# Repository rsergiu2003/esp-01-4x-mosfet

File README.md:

# esp-01-4x-mosfet
esp-01 extension board, with 4 mosfet transistors independently controlled, also has 1 power led and 4 status leds, and 3.3v stabilizations (can be powered up to 30V)

## Features
  - 4 mosfet transistors, connected to an pinheads
  - supports up to 30V DC (depending on the used mosfets)
  - no separate power needed for the ESP-01
  - 3.3 Voltage stabilizer
  - capacitor for voltage fluctuations
  - power indicator LED
  - status LED for each mosfet (so you can se if it's enabled or no)
  
## Testing
The board was tested with 12V comuper fans

## Software
Here are some repositories you can check out for using with this board.

## 3D Model

## More info
If you want more info feel free to leave me a message !

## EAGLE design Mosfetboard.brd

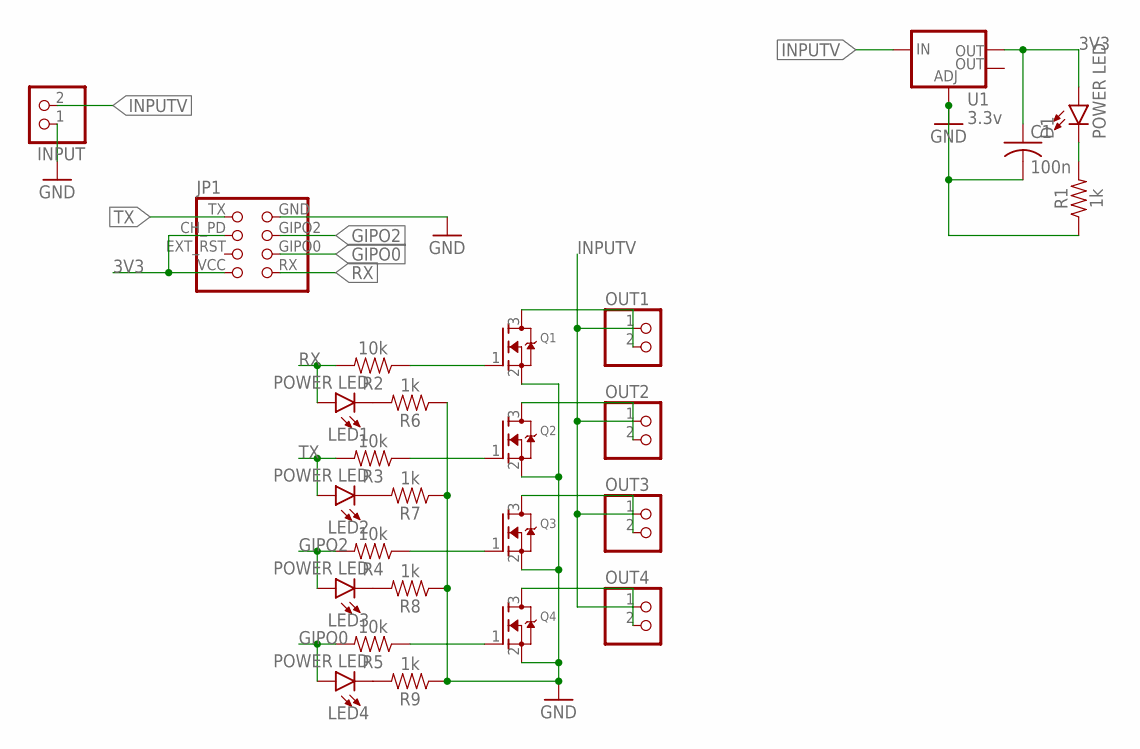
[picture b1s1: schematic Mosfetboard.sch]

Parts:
C1: 100n; C1206K
D1: POWER LED; LED-0805
INPUT: PINHD-1X2; 1X02
JP1: ESP-01-FEMALE
LED1, LED2, LED3, LED4: POWER LED; LED-0805
OUT1, OUT2, OUT3, OUT4: PINHD-1X2; 1X02
Q1, Q2, Q3, Q4: MOSFET-NREFLOW; SOT23
R1, R6, R7, R8, R9: 1k; 0805
R2, R3, R4, R5: 10k; 0805
U1: 3.3v; SOT223

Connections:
3V3: C1.1, D1.+ (A), JP1.CH_PD (CHIP_EN), JP1.VCC, U1.2 (OUT)
GIPO0: JP1.GIPO0, LED4.+ (A), R5.2
GIPO2: JP1.GIPO2, LED3.+ (A), R4.2
GND: C1.2, INPUT.1, JP1.GND, Q1.2 (S), Q2.2 (S), Q3.2 (S), Q4.2 (S), R1.1, R6.1, R7.1, R8.1, R9.1, U1.1 (ADJ)
INPUTV: INPUT.2, OUT1.1, OUT2.1, OUT3.1, OUT4.1, U1.3 (IN)
unnamed: OUT1.2, Q1.3 (D)
unnamed: OUT2.2, Q2.3 (D)
unnamed: OUT3.2, Q3.3 (D)
unnamed: OUT4.2, Q4.3 (D)
unnamed: D1.- (C), R1.2
unnamed: Q1.1 (G), R2.1
unnamed: Q2.1 (G), R3.1
unnamed: Q3.1 (G), R4.1
unnamed: Q4.1 (G), R5.1
unnamed: LED1.- (C), R6.2
unnamed: LED2.- (C), R7.2
unnamed: LED3.- (C), R8.2
unnamed: LED4.- (C), R9.2
RX: JP1.RX, LED1.+ (A), R2.2
TX: JP1.TX, LED2.+ (A), R3.2

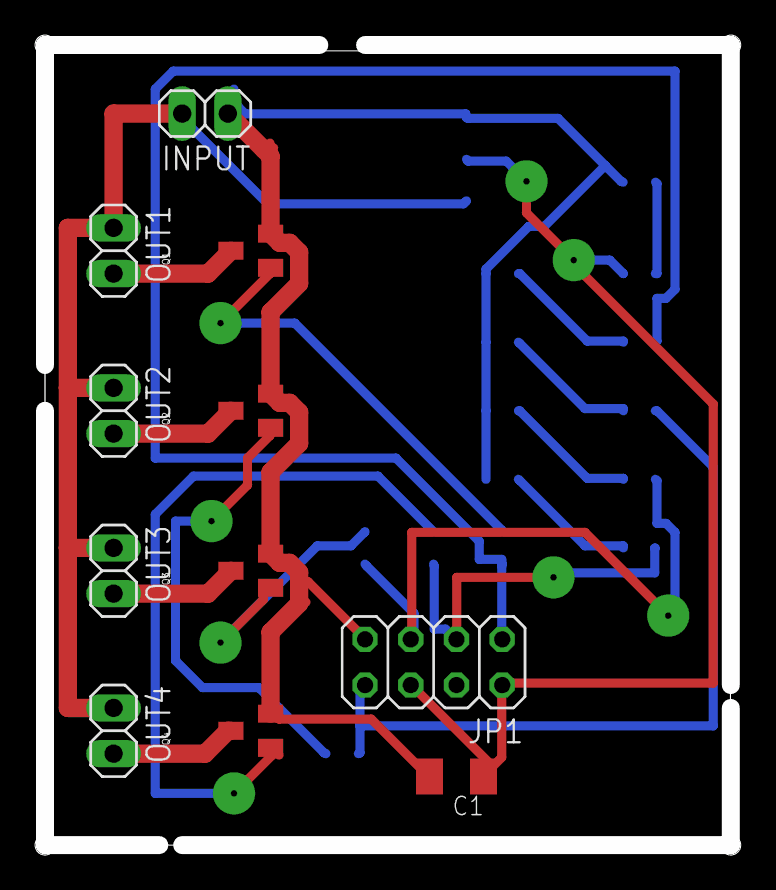
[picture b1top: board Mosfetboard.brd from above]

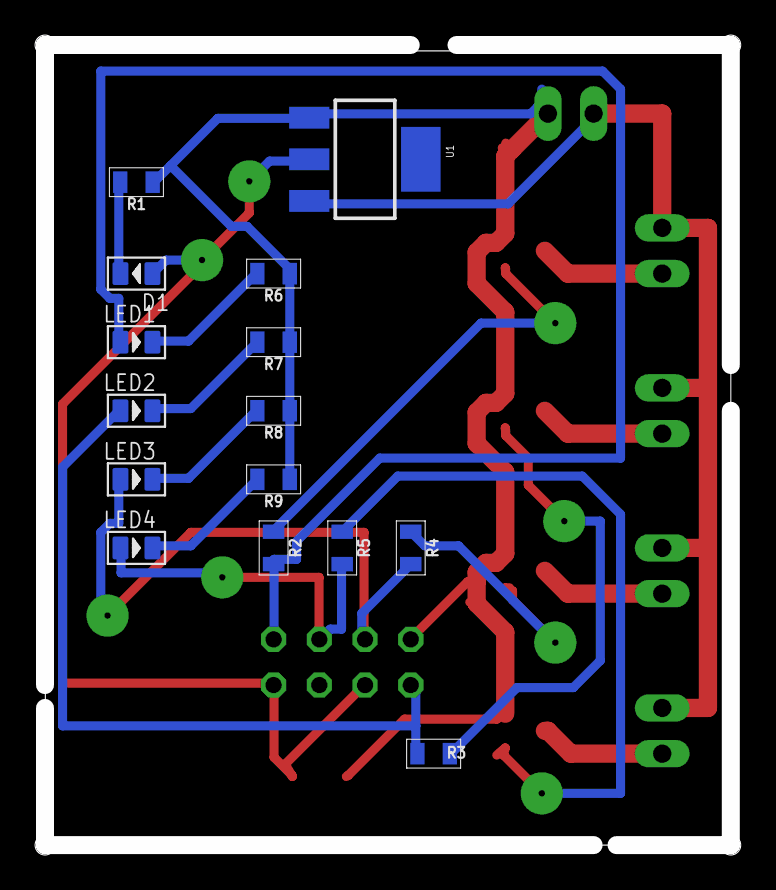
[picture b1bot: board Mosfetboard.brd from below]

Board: 2 copper layers, 38.1 x 44.5 mm, 26 parts (15 on the bottom side), 20 nets.

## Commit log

2019-01-17 ignore
2019-01-17 generate milling code
2019-01-17 versiune cu led-uri
2019-01-17 images
2019-05-01 add values to resistors
